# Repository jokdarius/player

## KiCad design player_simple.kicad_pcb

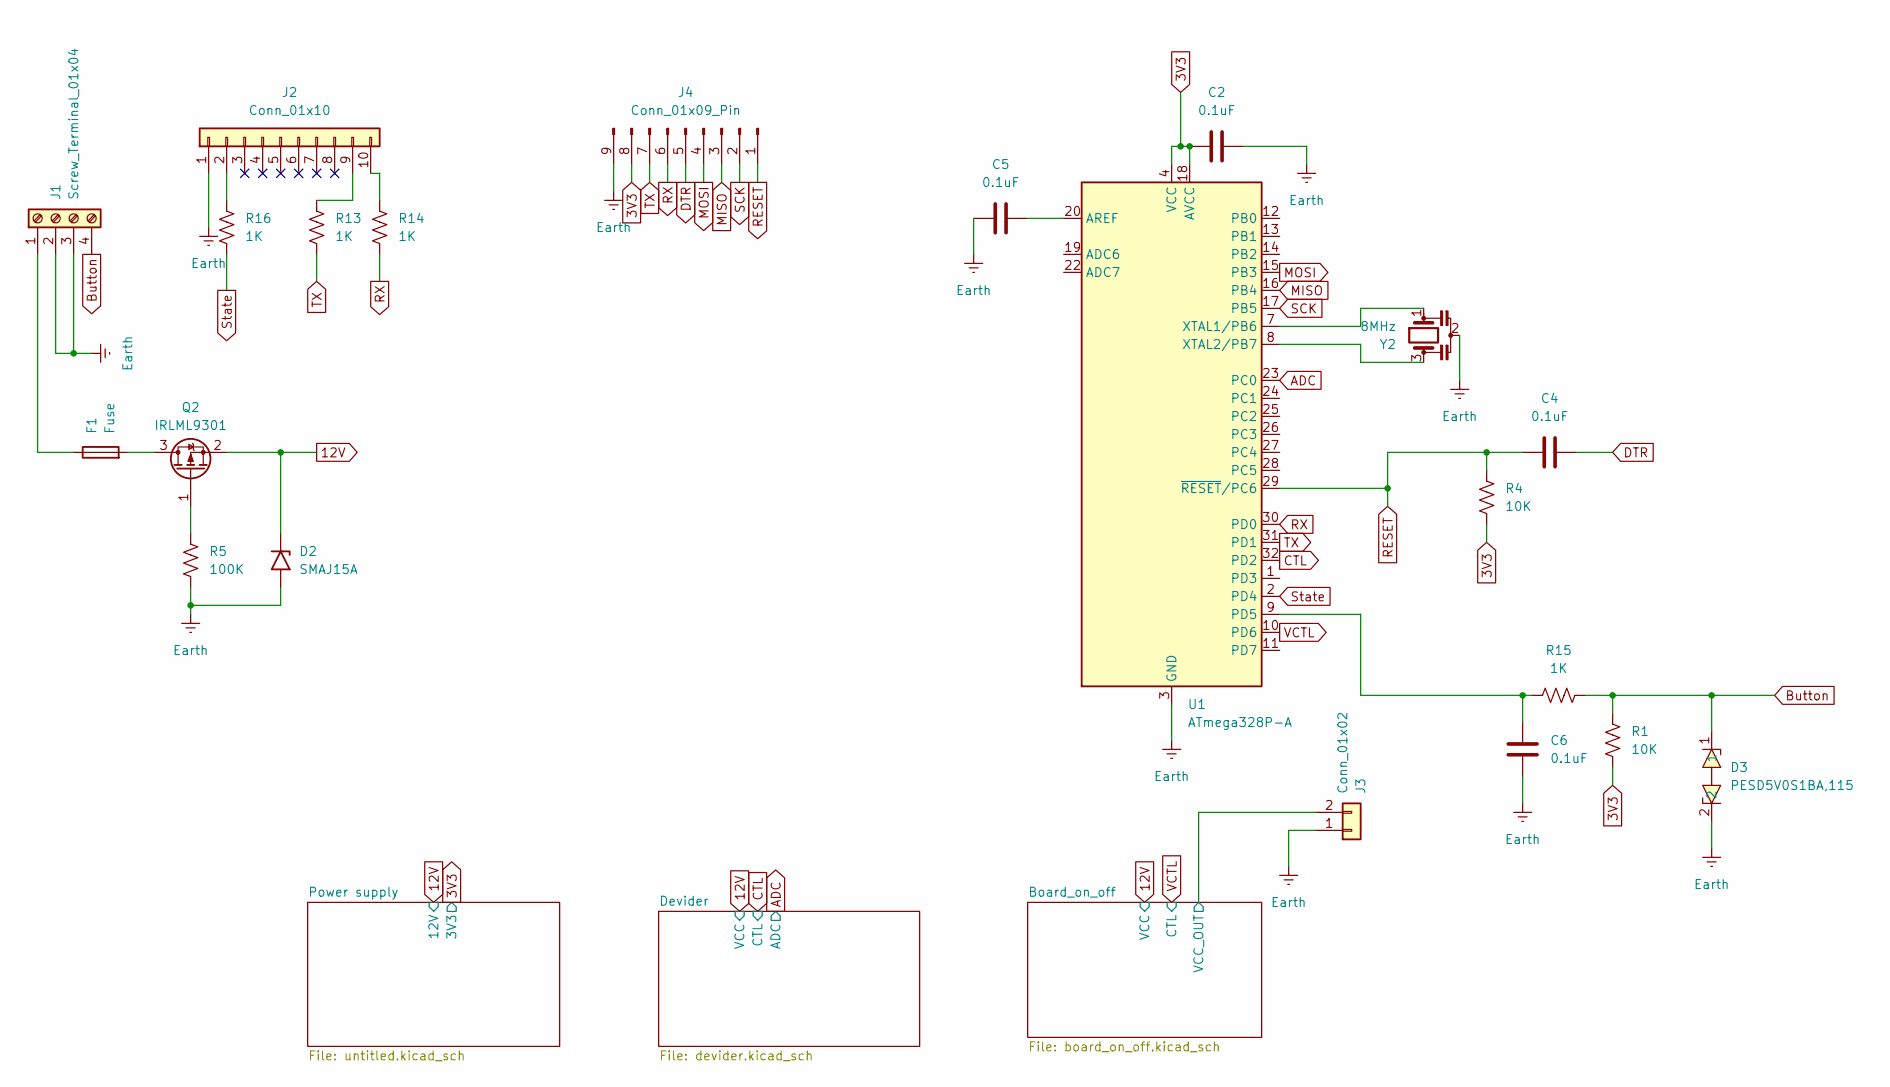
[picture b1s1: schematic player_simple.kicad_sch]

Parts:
C2, C4, C5, C6: 0.1uF; C_0805_2012Metric_Pad1.18x1.45mm_HandSolder
D2: SMAJ15A; D_SMA
D3: PESD5V0S1BA,115; D_SOD-323_HandSoldering; MPN PESD5V0S1BA,115; LCSC Part C19224
F1: Fuse; Fuse_1812_4532Metric_Pad1.30x3.40mm_HandSolder
J1: Screw_Terminal_01x04; TerminalBlock_Xinya_XY308-2.54-4P_1x04_P2.54mm_Horizontal
J2: Conn_01x10; PinHeader_1x10_P2.54mm_Vertical
J3: Conn_01x02; PinHeader_1x02_P2.54mm_Vertical
J4: Conn_01x09_Pin; PinHeader_1x09_P2.54mm_Vertical
Q2: IRLML9301; SOT-23
R1, R4: 10K; R_0805_2012Metric_Pad1.20x1.40mm_HandSolder
R5: 100K; R_0805_2012Metric_Pad1.20x1.40mm_HandSolder
R13, R14, R15, R16: 1K; R_0805_2012Metric_Pad1.20x1.40mm_HandSolder
U1: ATmega328P-A; TQFP-32_7x7mm_P0.8mm
Y2: 8MHz; Resonator_SMD_Murata_CSTxExxV-3Pin_3.0x1.1mm_HandSoldering

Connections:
3V3: C2.2, J4.8, R1.2, R4.2, U1.4 (VCC), U1.6 (VCC), U1.18 (AVCC); also elsewhere on the board
12V: D2.1 (A1), Q2.2 (S); also elsewhere on the board
/Board_on_off/VCC_OUT: J3.2; also elsewhere on the board
ADC: U1.23 (PC0); also elsewhere on the board
Button: D3.1, J1.4, R1.1, R15.1
CTL: U1.32 (PD2); also elsewhere on the board
DTR: C4.1, J4.5
Earth: C2.1, C5.2, C6.2, D2.2 (A2), D3.2, J1.2, J1.3, J2.1, J3.1, J4.9, R5.2, U1.3 (GND), U1.5 (GND), U1.21 (GND), Y2.2; also elsewhere on the board
MISO: J4.3, U1.16 (PB4)
MOSI: J4.4, U1.15 (PB3)
unnamed: F1.1, J1.1
unnamed: J2.2, R16.1
unnamed: J2.9, R13.1
unnamed: J2.10, R14.1
unnamed: F1.2, Q2.3 (D)
unnamed: Q2.1 (G), R5.1
unnamed: C5.1, U1.20 (AREF)
unnamed: C6.1, R15.2, U1.9 (PD5)
unnamed: U1.7 (XTAL1/PB6), Y2.1
unnamed: U1.8 (XTAL2/PB7), Y2.3
RESET: C4.2, J4.1, R4.1, U1.29 (~RESET/PC6)
RX: J4.6, R14.2, U1.30 (PD0)
SCK: J4.2, U1.17 (PB5)
State: R16.2, U1.2 (PD4)
TX: J4.7, R13.2, U1.31 (PD1)
VCTL: U1.10 (PD6); also elsewhere on the board

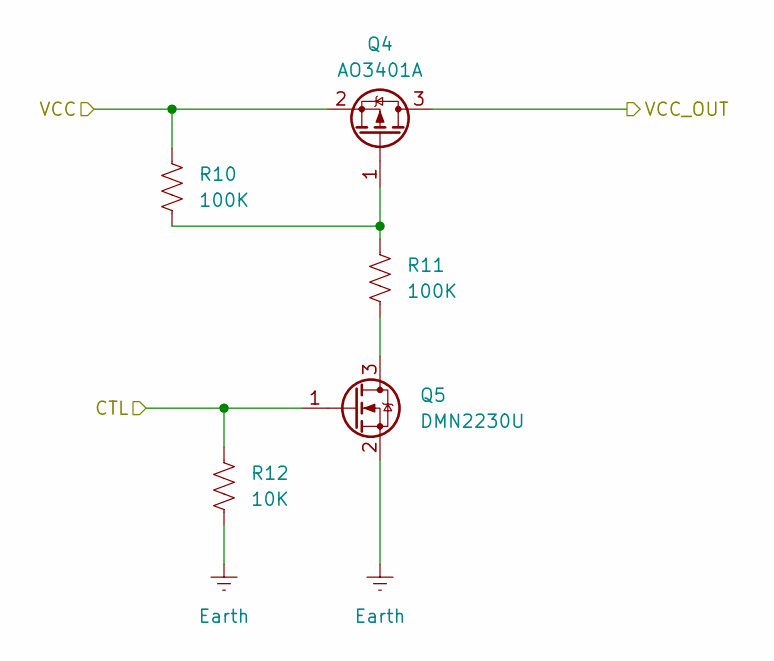
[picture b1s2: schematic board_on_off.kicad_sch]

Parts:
Q4: AO3401A; SOT-23
Q5: DMN2230U; SOT-23
R10, R11: 100K; R_0805_2012Metric_Pad1.20x1.40mm_HandSolder
R12: 10K; R_0805_2012Metric_Pad1.20x1.40mm_HandSolder

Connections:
12V: Q4.2 (S), R10.1; also elsewhere on the board
/Board_on_off/VCC_OUT: Q4.3 (D); also elsewhere on the board
Earth: Q5.2 (S), R12.2; also elsewhere on the board
unnamed: Q4.1 (G), R10.2, R11.1
unnamed: Q5.3 (D), R11.2
VCTL: Q5.1 (G), R12.1; also elsewhere on the board

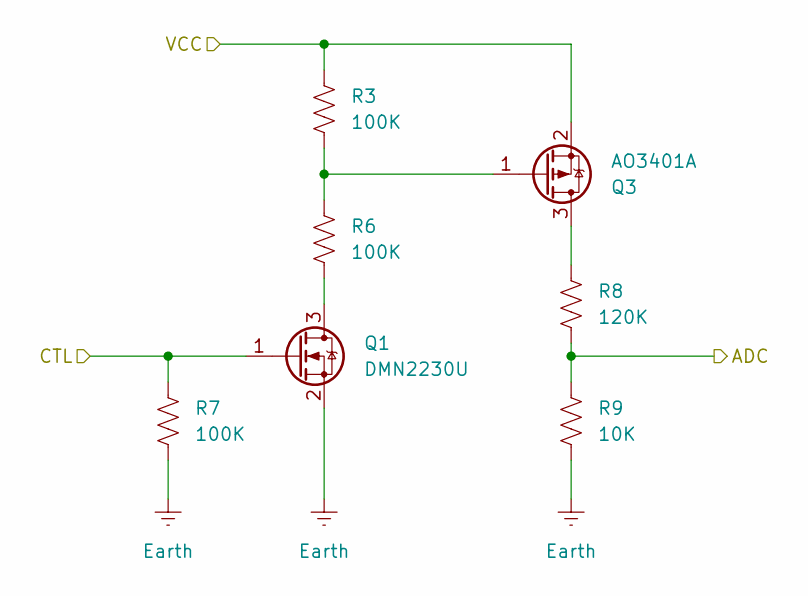
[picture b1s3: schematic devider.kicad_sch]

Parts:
Q1: DMN2230U; SOT-23
Q3: AO3401A; SOT-23
R3, R6, R7: 100K; R_0805_2012Metric_Pad1.20x1.40mm_HandSolder
R8: 120K; R_0805_2012Metric_Pad1.20x1.40mm_HandSolder
R9: 10K; R_0805_2012Metric_Pad1.20x1.40mm_HandSolder

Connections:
12V: Q3.2 (S), R3.1; also elsewhere on the board
ADC: R8.2, R9.1; also elsewhere on the board
CTL: Q1.1 (G), R7.1; also elsewhere on the board
Earth: Q1.2 (S), R7.2, R9.2; also elsewhere on the board
unnamed: Q1.3 (D), R6.2
unnamed: Q3.3 (D), R8.1
unnamed: Q3.1 (G), R3.2, R6.1

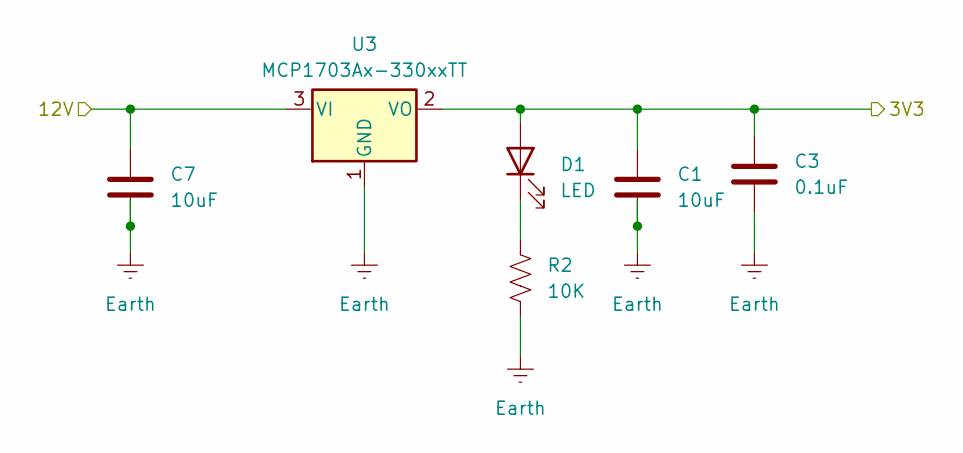
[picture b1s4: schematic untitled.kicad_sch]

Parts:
C1, C7: 10uF; C_0805_2012Metric_Pad1.18x1.45mm_HandSolder
C3: 0.1uF; C_0805_2012Metric_Pad1.18x1.45mm_HandSolder
D1: LED; LED_0805_2012Metric_Pad1.15x1.40mm_HandSolder
R2: 10K; R_0805_2012Metric_Pad1.20x1.40mm_HandSolder
U3: MCP1703Ax-330xxTT; SOT-23

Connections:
3V3: C1.1, C3.1, D1.2 (A), U3.2 (VO); also elsewhere on the board
12V: C7.1, U3.3 (VI); also elsewhere on the board
Earth: C1.2, C3.2, C7.2, R2.2, U3.1 (GND); also elsewhere on the board
unnamed: D1.1 (K), R2.1

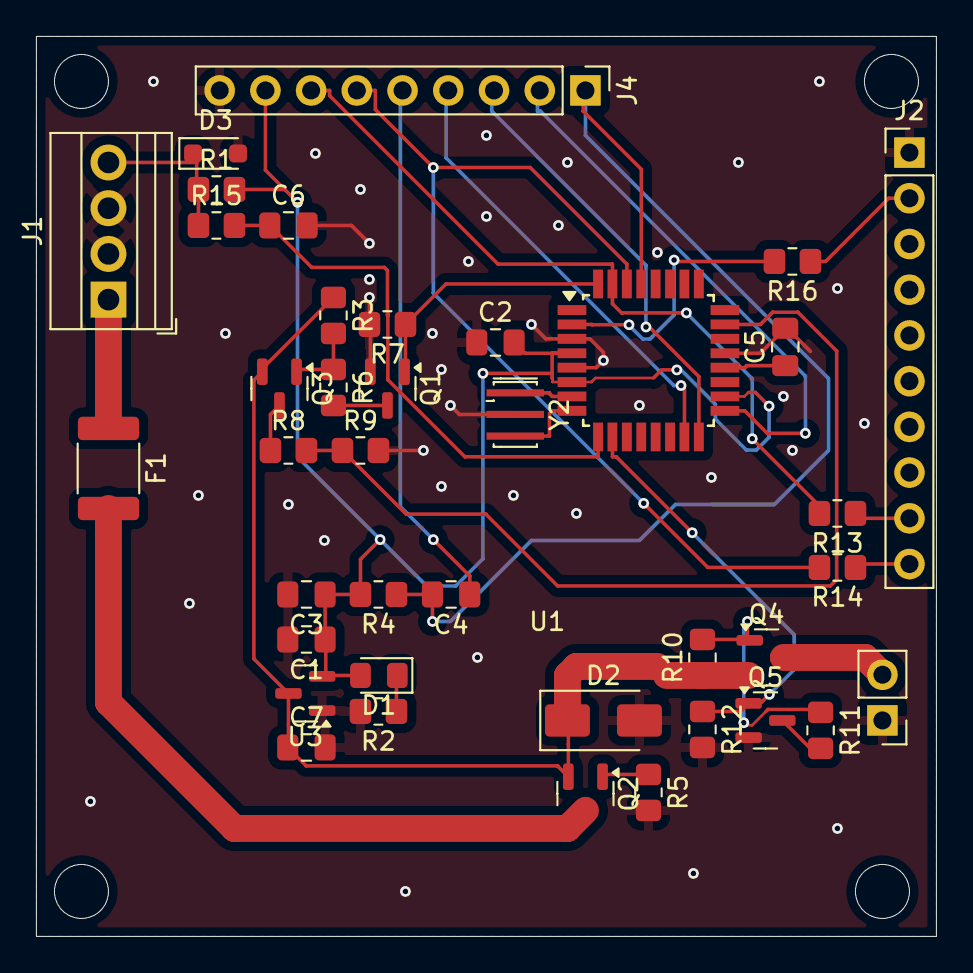
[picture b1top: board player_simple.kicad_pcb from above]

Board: 2 copper layers, 50.0 x 50.0 mm, 39 parts (0 on the bottom side), 32 nets.

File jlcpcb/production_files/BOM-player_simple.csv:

Comment,Designator,Footprint,LCSC,Quantity
0.1uF,"C2,C3,C4,C5,C6",C_0805_2012Metric_Pad1.18x1.45mm_HandSolder,C49678,5
100K,"R10,R11,R3,R5,R6,R7",R_0805_2012Metric_Pad1.20x1.40mm_HandSolder,C149504,6
10K,"R1,R12,R2,R4",R_0805_2012Metric_Pad1.20x1.40mm_HandSolder,C17414,4
10uF,"C1,C7",C_0805_2012Metric_Pad1.18x1.45mm_HandSolder,C15850,2
1K,"R13,R14,R15,R16",R_0805_2012Metric_Pad1.20x1.40mm_HandSolder,C17513,4
8MHz,Y2,Resonator_SMD_Murata_CSTxExxV-3Pin_3.0x1.1mm_HandSoldering,C341524,1
AO3401A,"Q3,Q4",SOT-23,C15127,2
ATmega328P-A,U1,TQFP-32_7x7mm_P0.8mm,C618732,1
DMN2230U,"Q1,Q5",SOT-23,C516590,2
Fuse,F1,Fuse_1812_4532Metric_Pad1.30x3.40mm_HandSolder,C2649921,1
IRLML9301,Q2,SOT-23,C5338294,1
LED,D1,LED_0805_2012Metric_Pad1.15x1.40mm_HandSolder,C2297,1
MCP1703Ax-330xxTT,U3,SOT-23,C144183,1
"PESD5V0S1BA,115",D3,D_SOD-323_HandSoldering,C19224,1
SMAJ15A,D2,D_SMA,C908769,1
120K,R8,R_0805_2012Metric_Pad1.20x1.40mm_HandSolder,,1
10K,R9,R_0805_2012Metric_Pad1.20x1.40mm_HandSolder,,1
Screw_Terminal_01x04,J1,TerminalBlock_Xinya_XY308-2.54-4P_1x04_P2.54mm_Horizontal,,1
Conn_01x02,J3,PinHeader_1x02_P2.54mm_Vertical,,1
Conn_01x10,J2,PinHeader_1x10_P2.54mm_Vertical,,1
Conn_01x09_Pin,J4,PinHeader_1x09_P2.54mm_Vertical,,1
